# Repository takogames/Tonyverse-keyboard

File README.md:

# this board currently has no firmware, because i never made it, use at your own risk
- instead, try bbsteno from mechwild.

# What is tonyverse?

Tonyverse is a new budget stenography keyboard, designed to be the best bang-for-your-buck for new steno users.

## Features
- Choc switches (recomended choc pinks)
- Cheap.
... yeah, that's pretty much it, shout out to the bbsteno, im planning on selling these eventually, always opensource.

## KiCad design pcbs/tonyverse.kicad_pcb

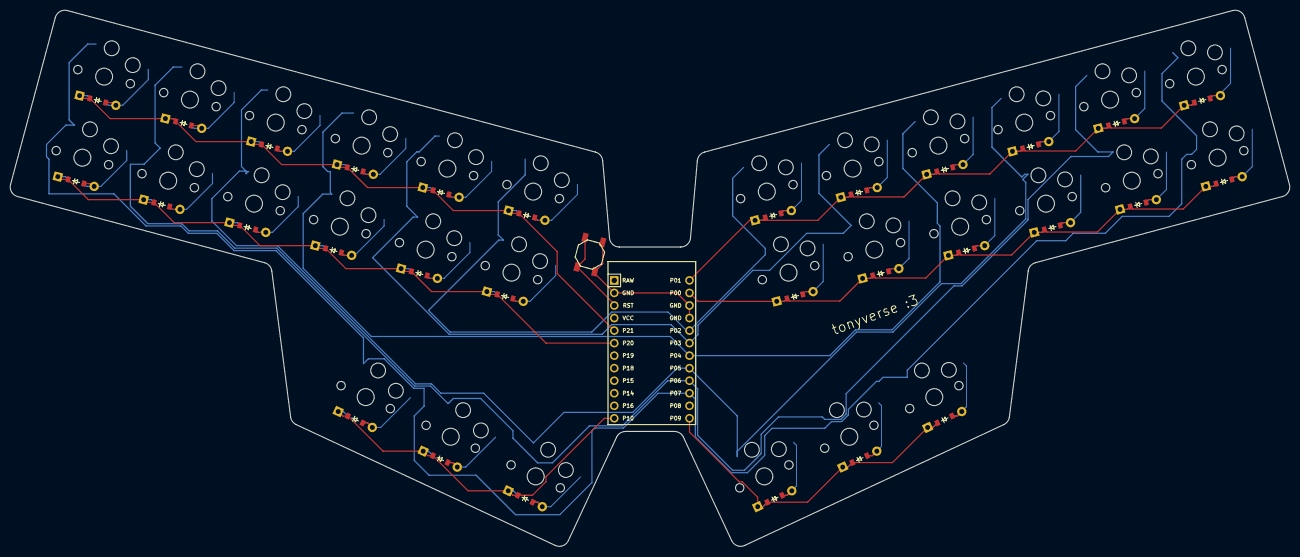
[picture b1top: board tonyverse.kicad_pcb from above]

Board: 2 copper layers, 259.2 x 108.6 mm, 62 parts (0 on the bottom side), 44 nets.

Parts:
B1: SW_TACT_ALPS_SKQGABE010
D1, D2, D3, D4, D5, D6, D7, D8, D9, D10, D11, D12, D13, D14, D15, D16, D17, D18, D19, D20, D21, D22, D23, D24, D25, D26, D27, D28, D29, D30: ComboDiode
MCU1: ProMicro
S1, S2, S3, S4, S5, S6, S7, S8, S9, S10, S11, S12, S13, S14, S15, S16, S17, S18, S19, S20, S21, S22, S23, S24, S25, S26, S27, S28, S29, S30: PG1350

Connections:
GND: B1.1, MCU1.2, MCU1.15, MCU1.16
P0: D16.1, D18.1, D20.1, D22.1, D24.1, D26.1, MCU1.14
P1: D17.1, D19.1, D21.1, D23.1, D25.1, D27.1, MCU1.13
P2: MCU1.17, S11.1, S12.1, S26.1, S27.1
P3: MCU1.18, S9.1, S10.1, S24.1, S25.1
P4: MCU1.19, S7.1, S8.1, S22.1, S23.1
P5: MCU1.20, S5.1, S6.1, S15.1, S20.1, S21.1, S30.1
P6: MCU1.21, S3.1, S4.1, S14.1, S18.1, S19.1, S29.1
P7: MCU1.22, S1.1, S2.1, S13.1, S16.1, S17.1, S28.1
P9: D28.1, D29.1, D30.1, MCU1.24
P10: D13.1, D14.1, D15.1, MCU1.12
P20: D1.1, D3.1, D5.1, D7.1, D9.1, D11.1, MCU1.6
P21: D2.1, D4.1, D6.1, D8.1, D10.1, D12.1, MCU1.5
RST: B1.2, MCU1.3
better_bottom: D5.2, S5.2
better_top: D6.2, S6.2
far_thumb: D15.2, S15.2
home_thumb: D14.2, S14.2
index_bottom: D9.2, S9.2
index_top: D10.2, S10.2
inner_bottom: D11.2, S11.2
inner_top: D12.2, S12.2
middle_bottom: D7.2, S7.2
middle_top: D8.2, S8.2
mirror_better_bottom: D20.2, S20.2
mirror_better_top: D21.2, S21.2
mirror_far_thumb: D30.2, S30.2
mirror_home_thumb: D29.2, S29.2
mirror_index_bottom: D24.2, S24.2
mirror_index_top: D25.2, S25.2
mirror_inner_bottom: D26.2, S26.2
mirror_inner_top: D27.2, S27.2
mirror_middle_bottom: D22.2, S22.2
mirror_middle_top: D23.2, S23.2
mirror_near_thumb: D28.2, S28.2
mirror_pinky_bottom: D16.2, S16.2
mirror_pinky_top: D17.2, S17.2
mirror_ring_bottom: D18.2, S18.2
mirror_ring_top: D19.2, S19.2
near_thumb: D13.2, S13.2
pinky_bottom: D1.2, S1.2
pinky_top: D2.2, S2.2
ring_bottom: D3.2, S3.2
ring_top: D4.2, S4.2

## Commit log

2024-08-12 sample
